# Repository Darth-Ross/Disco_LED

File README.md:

# Quick description 

This is a design for a IR RGB LEDstrip driver which uses a 24 key RGB remote. It can display 16 predetermined static colours, change brightness, turn off and on again while remembering the last colour and display special functions like for example smooth colour change or colour flashing. 

The repo includes both hardware and software design which you can either use directly or include in your own projects.

# Licenses

The software is licensed under the GNU General Public License V3.0 and the hardware is licensed under the CERN Open Hardware License V1.2. See the license files in each folder for more information.

# Libraries 

These are all the libraries I have used that were made by other users.
- https://github.com/electrobs/AVR-LIBRARY-IR_REMOTE_RECV

# Hardware changelog
#### V1.0
- Added electrical schematic
- Added PCB design
- Added licensing
#### V1.0.1
- Added gerber files 
- Added 3D renders 
#### V1.1
- Fixed connection error for ICSP port

# Software changelog
#### V1.0
- Basic feature implementation
- Added 24 key RGB remote support
- Added ATmega328p support
- Added licensing
#### V1.1
- Added first implementation of CMD_REPEAT functionality
- Reworked the brightness system to use percentage instead of RGB values. 

#### Known bugs
- CMD_REPEAT remembers the command BPLUS OR BMIN even after pressing other commands. This will cause the BPLUS or BMIN command to be executed if other commands are repeated.

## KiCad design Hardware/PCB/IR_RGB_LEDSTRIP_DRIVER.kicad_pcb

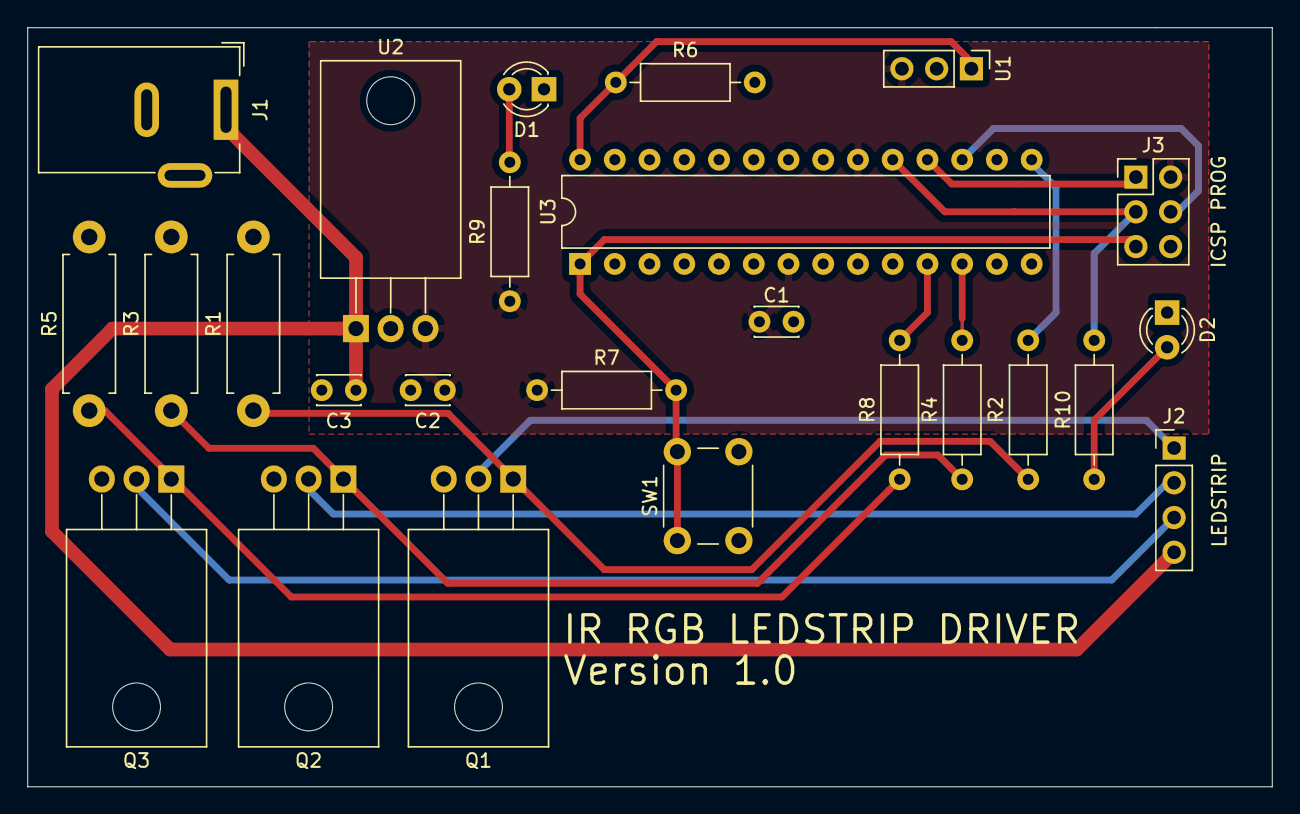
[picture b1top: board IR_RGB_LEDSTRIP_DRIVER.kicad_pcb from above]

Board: 2 copper layers, 91.0 x 55.5 mm, 25 parts (0 on the bottom side), 19 nets.

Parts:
C1: 100n; C_Disc_D3.0mm_W2.0mm_P2.50mm
C2, C3: 0.1u; C_Disc_D3.0mm_W2.0mm_P2.50mm
D1, D2: LED; LED_D3.0mm
J1: Barrel_Jack; BarrelJack_Wuerth_6941xx301002
J2: Conn_01x04_Female; PinHeader_1x04_P2.54mm_Vertical
J3: ICSP connector; PinHeader_2x03_P2.54mm_Vertical
Q1, Q2, Q3: IRLZ34N; TO-220-3_Horizontal_TabDown
R1, R3, R5: 10K; R_Axial_DIN0411_L9.9mm_D3.6mm_P12.70mm_Horizontal
R2, R4, R6, R7, R8, R9, R10: 1K; R_Axial_DIN0207_L6.3mm_D2.5mm_P10.16mm_Horizontal
SW1: SW_RESET; SW_PUSH_6mm_H5mm
U1: TSOP134xx; PinHeader_1x03_P2.54mm_Vertical
U2: L7805; TO-220-3_Horizontal_TabDown
U3: ATmega328P-PU; DIP-28_W7.62mm

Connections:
+12V: C3.1, J1.1, J2.4, U2.1
BLUE_SIGNAL: R8.2, U3.11
GND: C1.2, C2.2, C3.2, D1.1, D2.1, J1.2, J3.6, Q1.3, Q2.3, Q3.3, R1.2, R3.2, R5.2, R6.2, SW1.2, U1.2, U2.2, U3.8, U3.21, U3.22
GREEN_SIGNAL: R2.2, U3.15
unnamed: D1.2, R9.2
unnamed: D2.2, R10.2
unnamed: J2.1, Q1.2
unnamed: J2.2, Q2.2
unnamed: J2.3, Q3.2
unnamed: J3.1, U3.18
unnamed: J3.3, R10.1, U3.19
unnamed: J3.4, U3.17
unnamed: J3.5, R7.2, SW1.1, U3.1
unnamed: Q1.1, R1.1, R2.1
unnamed: Q2.1, R3.1, R4.1
unnamed: Q3.1, R5.1, R8.1
unnamed: R6.1, U1.1, U3.28
RED_SIGNAL: R4.2, U3.12
VCC: C1.1, C2.1, J3.2, R7.1, R9.1, U1.3, U2.3, U3.7, U3.20

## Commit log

2018-01-30 Initial commit
    Initializing the repo.
2018-02-21 Initial prototype function commit
    Commition for the first function prototype.
2018-02-21 Initial commit v2
    Redoing the initial commit
2018-02-21 Revert "Initial commit v2"
    This reverts commit dc25a86f87c63cb3420241aa34d9152f8fef500c.
2018-02-21 test commit
2018-02-21 Revert "test commit"
    This reverts commit 074869fcf5e54629d168ce7b026dc83389a1620b.
2018-02-21 Initial commit v2
2018-02-21 Removing files
    test.c & test.h weren't supposed to be in main.
2018-02-21 Initial commit v2.1
2018-02-21 inital commit 2.2
2018-02-21 initial commit v2.3
2018-02-21 commit fix
2018-02-21 Repo reorganisation
    This is a reorganisation of my repo so it includes the hardware as well.
2018-02-21 repo fix
2018-02-22 Prototype RGB function
2018-02-22 Revert "Prototype RGB function"
    This reverts commit 518bd678ab81e604af471f3ae03ca95bfdcec0f7.
2018-02-22 Added prototype function RGB
2018-04-15 New pwm function prototype 1.
2018-04-16 Added RGB function prototype v0.1
2018-08-21 Add libaries
2019-07-11 Adding first software prototype
2019-07-11 Removed unnecesary files
2019-07-12 Fixed typos
2019-07-12 Removed unneccesary files
2019-07-12 v1.0
2019-07-20 Added hardeware design
2019-07-20 Changed license file
2019-07-22 Added PCB gerbers and renders
2019-08-01 added the kicad file for the PCB design and added some comments to disco_functions
2019-08-31 Added OK LED to check if the microcontroller is working OK
2019-10-07 Fixed connection error for the ICSP port
2019-10-16 Added first version of CMD_REPEAT and changed the brightness system to use percentage instead of RGB values.
2019-10-16 Fixed comments
